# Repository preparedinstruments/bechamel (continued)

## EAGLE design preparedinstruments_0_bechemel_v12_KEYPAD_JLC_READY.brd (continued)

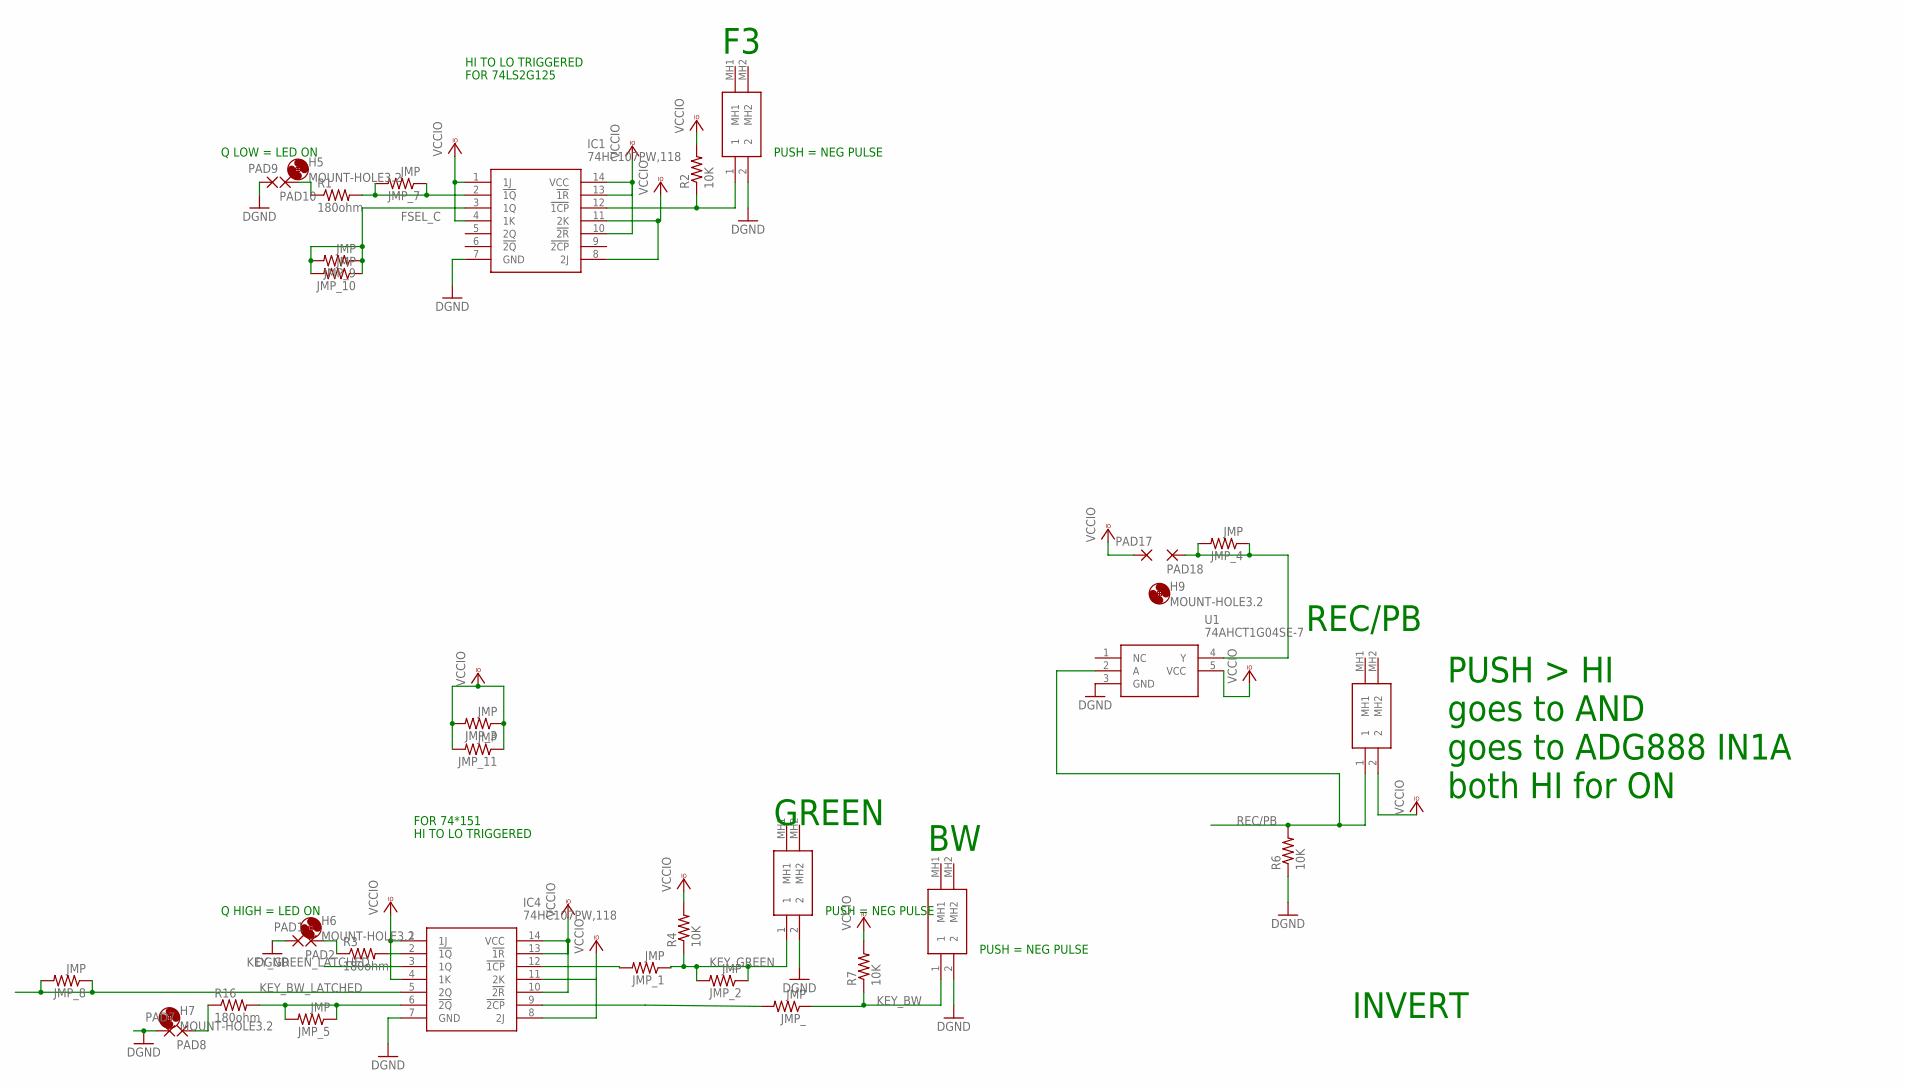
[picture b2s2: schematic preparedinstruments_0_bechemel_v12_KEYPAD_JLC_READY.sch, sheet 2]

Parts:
H5, H6, H7, H9: MOUNT-HOLE3.2; 3,2
IC1, IC4: 74HC107PW,118; SOP65P640X110-14N
JMP_, JMP_1, JMP_2, JMP_3, JMP_4, JMP_5, JMP_7, JMP_8, JMP_9, JMP_10, JMP_11: JMP; R0805
PAD1, PAD2, PAD7, PAD8, PAD9, PAD10, PAD17, PAD18: SMD2; SMD1,27-2,54
R1, R3, R16: 180ohm; R0805
R2, R4, R6, R7: 10K; R0805
S1, S2, S4, S5: MX1A-11NW; MX1A11NW
U1: 74AHCT1G04SE-7; SOT65P210X110-5N

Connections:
DGND: IC1.7 (GND), IC4.7 (GND), PAD1.1, PAD7.1, PAD9.1, R6.1, S1.2, S2.2, S4.2, U1.3 (GND); also elsewhere on the board
FSEL_C: IC1.3 (1Q), JMP_9.1, JMP_9.2, JMP_10.1, JMP_10.2; also elsewhere on the board
KEY_BW: JMP_.1, R7.1, S4.1; also elsewhere on the board
KEY_BW_LATCHED: IC4.5 (2Q), JMP_8.1, JMP_8.2; also elsewhere on the board
KEY_GREEN: JMP_1.1, JMP_2.1, JMP_2.2, R4.1, S2.1; also elsewhere on the board
KEY_GREEN_LATCHED: IC4.3 (1Q); also elsewhere on the board
unnamed: PAD10.1, R1.1
unnamed: IC1.2 (!1Q), JMP_7.1, JMP_7.2, R1.2
unnamed: JMP_4.1, JMP_4.2, PAD18.1, U1.4 (Y)
unnamed: IC1.12 (!1CP), R2.1, S1.1
unnamed: PAD2.1, R3.1
unnamed: IC4.2 (!1Q), R3.2
unnamed: PAD8.1, R16.1
unnamed: IC4.6 (!2Q), JMP_5.1, JMP_5.2, R16.2
unnamed: IC4.9 (!2CP), JMP_.2
unnamed: IC4.12 (!1CP), JMP_1.2
REC/PB: R6.2, S5.1, U1.2 (A); also elsewhere on the board
VCCIO: IC1.1 (1J), IC1.4 (1K), IC1.8 (2J), IC1.10 (!2R), IC1.11 (2K), IC1.13 (!1R), IC1.14 (VCC), IC4.1 (1J), IC4.4 (1K), IC4.8 (2J), IC4.10 (!2R), IC4.11 (2K), IC4.13 (!1R), IC4.14 (VCC), JMP_3.1, JMP_3.2, JMP_11.1, JMP_11.2, PAD17.1, R2.2, R4.2, R7.2, S5.2, U1.5 (VCC); also elsewhere on the board

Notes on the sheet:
PUSH = NEG PULSE
Q LOW = LED ON
FOR 74LS2G125
FOR 74*151
Q HIGH = LED ON
GREEN
REC/PB
PUSH > HI goes to AND goes to ADG888 IN1A both HI for ON
INVERT
HI TO LO TRIGGERED

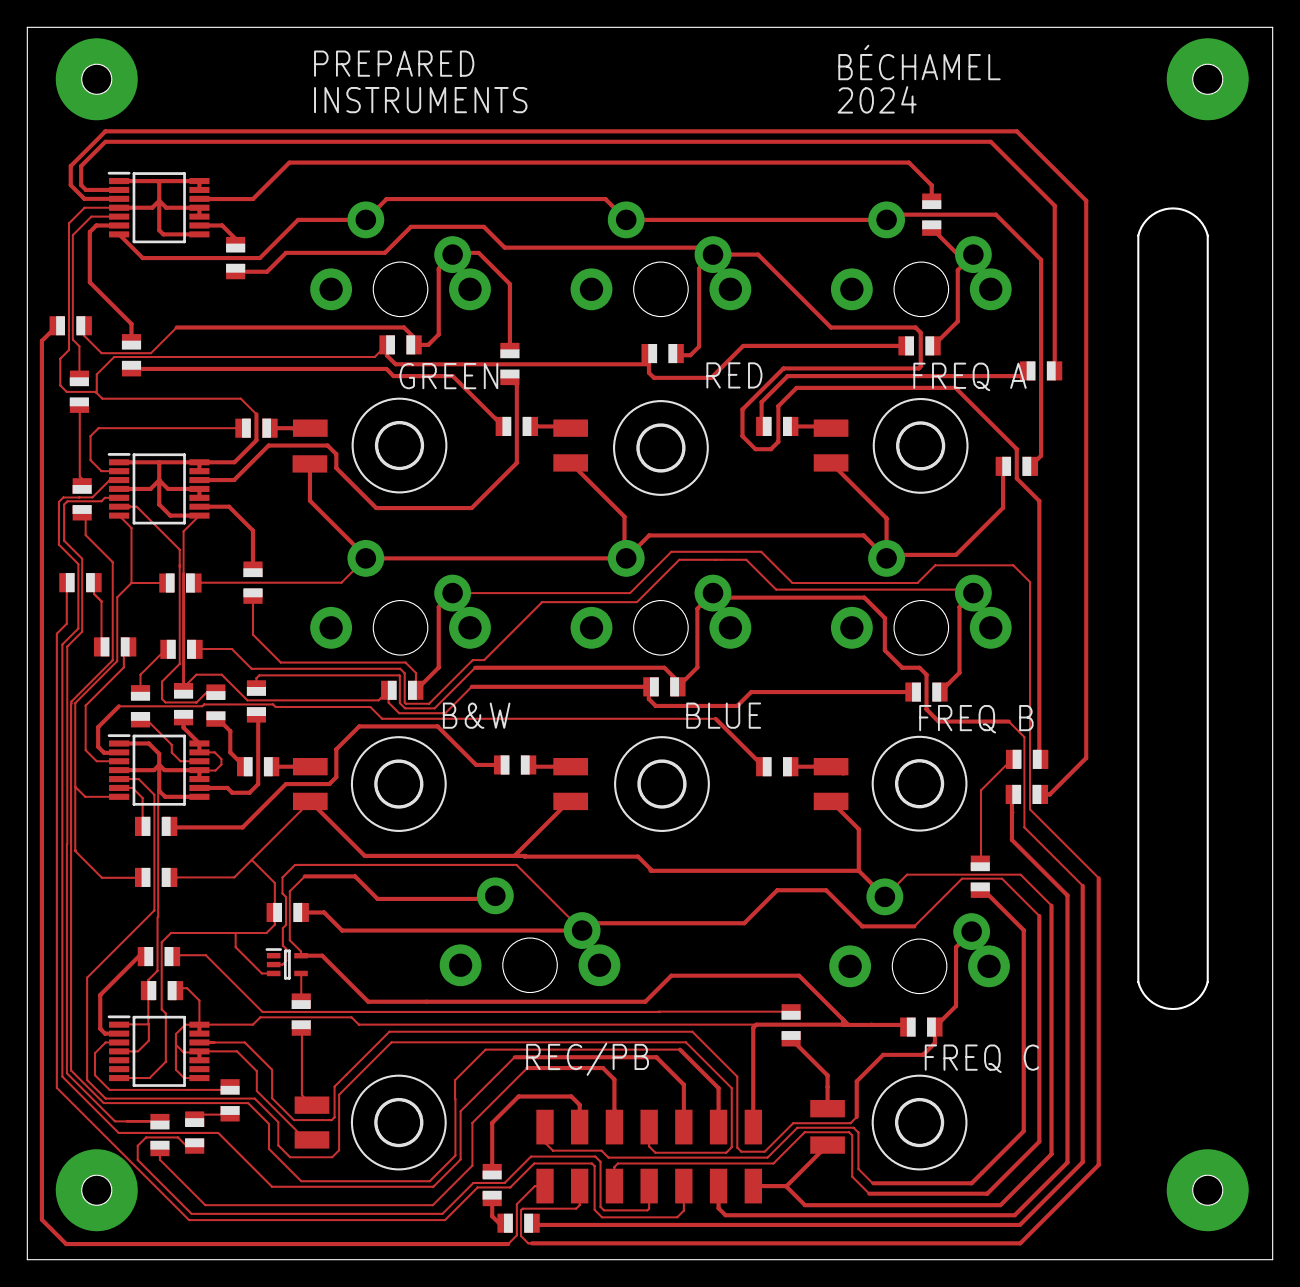
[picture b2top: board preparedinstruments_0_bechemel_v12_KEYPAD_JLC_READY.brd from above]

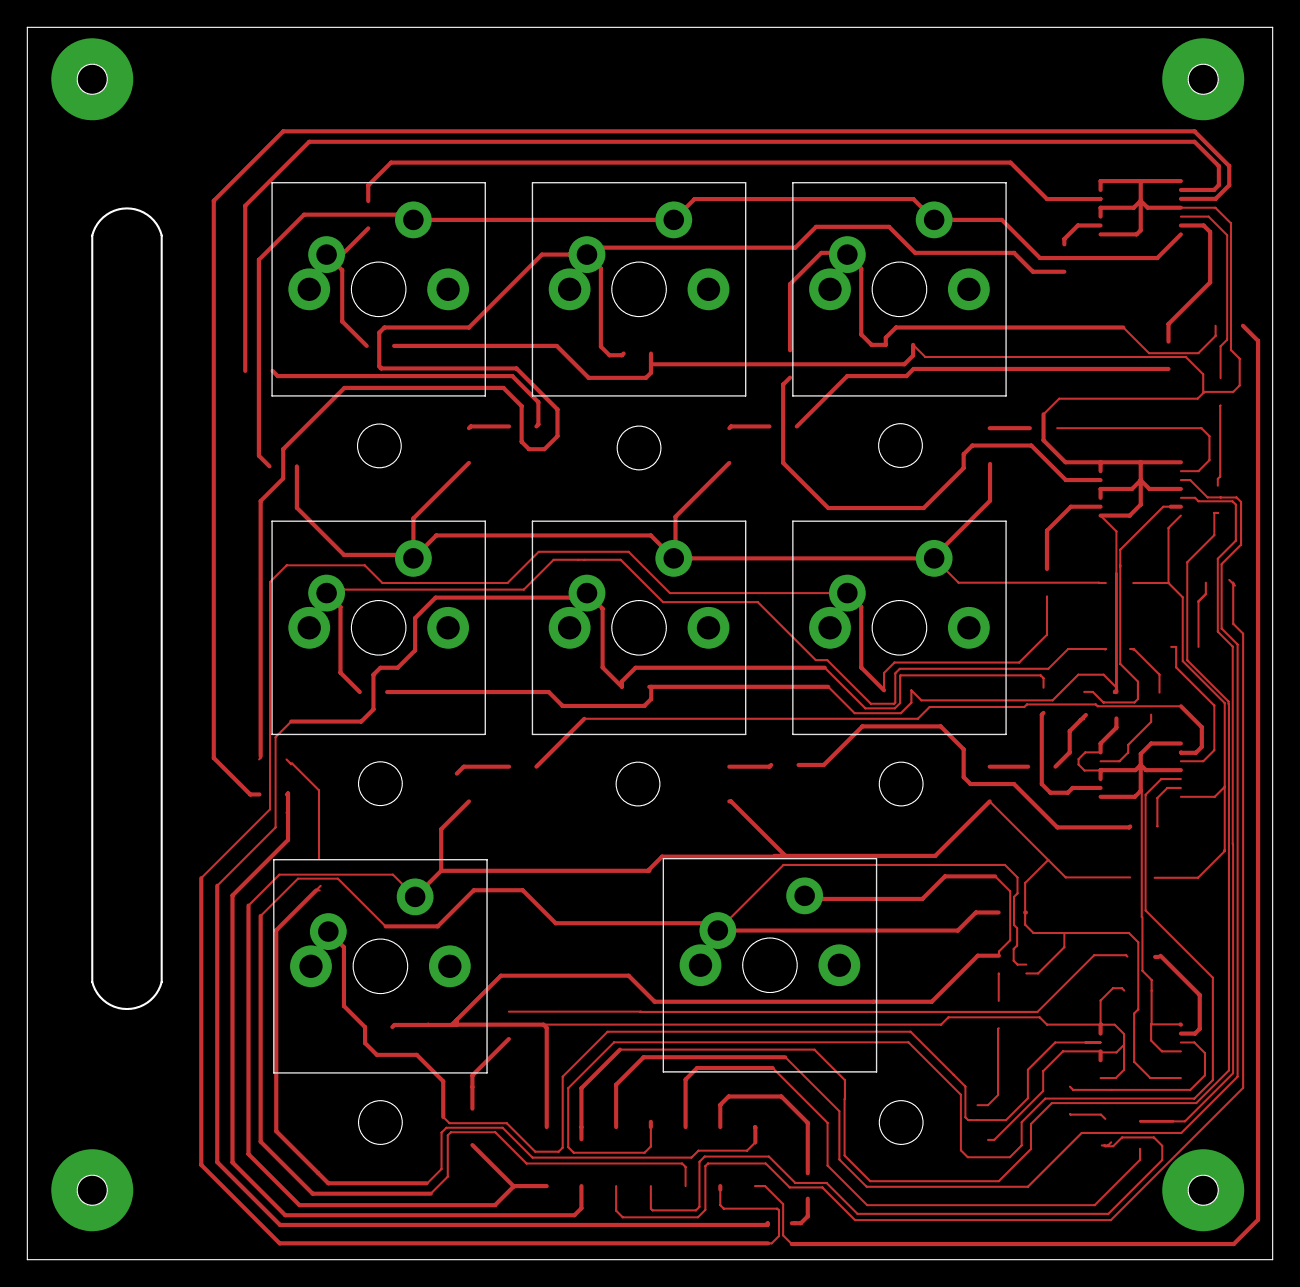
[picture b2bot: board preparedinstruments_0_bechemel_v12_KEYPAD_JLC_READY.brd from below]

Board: 2 copper layers, 91.1 x 90.2 mm, 101 parts (8 on the bottom side), 38 nets.

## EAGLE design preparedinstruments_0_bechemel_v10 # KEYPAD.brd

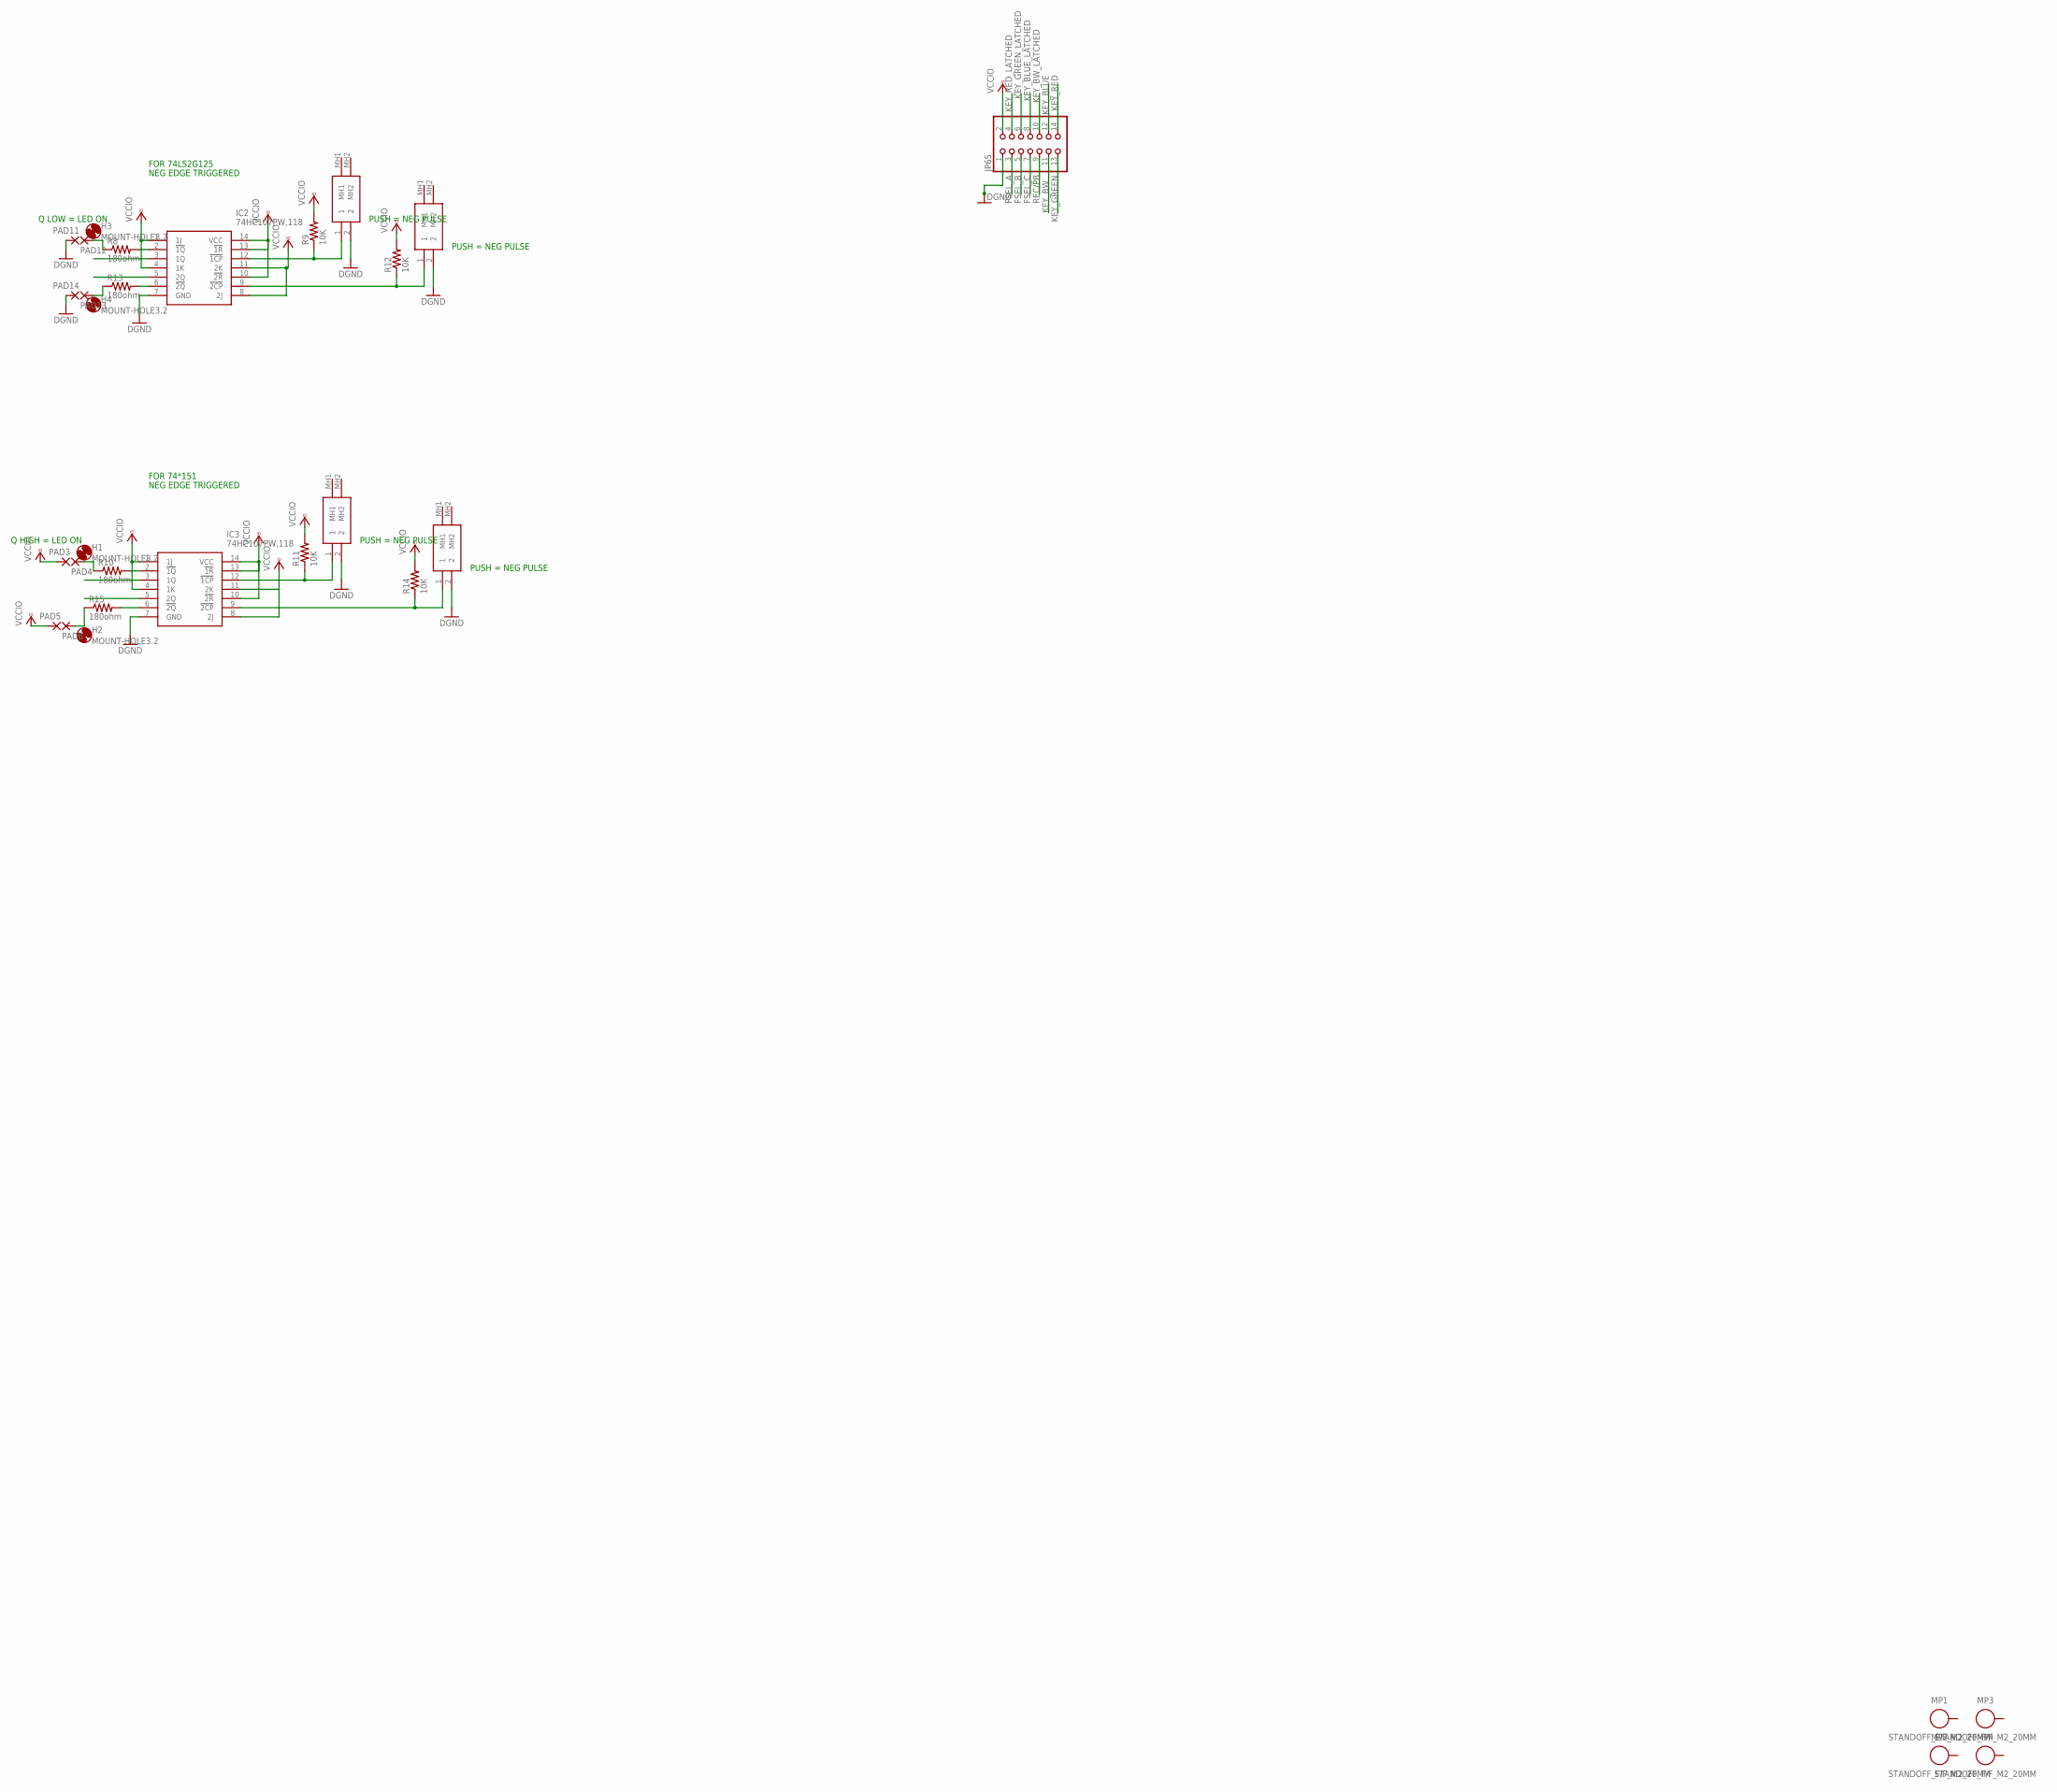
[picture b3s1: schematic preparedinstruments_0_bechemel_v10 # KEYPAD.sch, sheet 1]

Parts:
H1, H2, H3, H4: MOUNT-HOLE3.2; 3,2
IC2, IC3: 74HC107PW,118; SOP65P640X110-14N
JP65: PINHD-2X7; 2X07
MP1, MP2, MP3, MP4: STANDOFF_F/F_M2_20MM; STANDOFF_HEX_FEMALE_400X2000_M2X0.4_MTGP600H220
PAD3, PAD4, PAD5, PAD6, PAD11, PAD12, PAD13, PAD14: SMD2; SMD1,27-2,54
R8, R10, R13, R15: 180ohm; R0805
R9, R11, R12, R14: 10K; R0805
S6, S7, S8, S9: MX1A-11NW; MX1A11NW

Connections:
DGND: IC2.7 (GND), IC3.7 (GND), JP65.1, PAD11.1, PAD14.1, S6.2, S7.2, S8.2, S9.2; also elsewhere on the board
FSEL_A: JP65.3
FSEL_B: JP65.5
FSEL_C: JP65.7
KEY_BLUE: JP65.12
KEY_BLUE_LATCHED: JP65.8
KEY_BW: JP65.11
KEY_BW_LATCHED: JP65.10
KEY_GREEN: JP65.13
KEY_GREEN_LATCHED: JP65.6
KEY_RED: JP65.14
KEY_RED_LATCHED: JP65.4
unnamed: PAD12.1, R8.1
unnamed: IC2.2 (!1Q), R8.2
unnamed: IC2.12 (!1CP), R9.1, S6.1
unnamed: PAD4.1, R10.1
unnamed: IC3.2 (!1Q), R10.2
unnamed: IC3.12 (!1CP), R11.1, S7.1
unnamed: IC2.9 (!2CP), R12.1, S8.1
unnamed: PAD13.1, R13.1
unnamed: IC2.6 (!2Q), R13.2
unnamed: IC3.9 (!2CP), R14.1, S9.1
unnamed: PAD6.1, R15.1
unnamed: IC3.6 (!2Q), R15.2
REC/PB: JP65.9
VCCIO: IC2.1 (1J), IC2.4 (1K), IC2.8 (2J), IC2.10 (!2R), IC2.11 (2K), IC2.13 (!1R), IC2.14 (VCC), IC3.1 (1J), IC3.4 (1K), IC3.8 (2J), IC3.10 (!2R), IC3.11 (2K), IC3.13 (!1R), IC3.14 (VCC), JP65.2, PAD3.1, PAD5.1, R9.2, R11.2, R12.2, R14.2; also elsewhere on the board

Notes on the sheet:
NEG EDGE TRIGGERED
PUSH = NEG PULSE
Q LOW = LED ON
FOR 74LS2G125
FOR 74*151
Q HIGH = LED ON

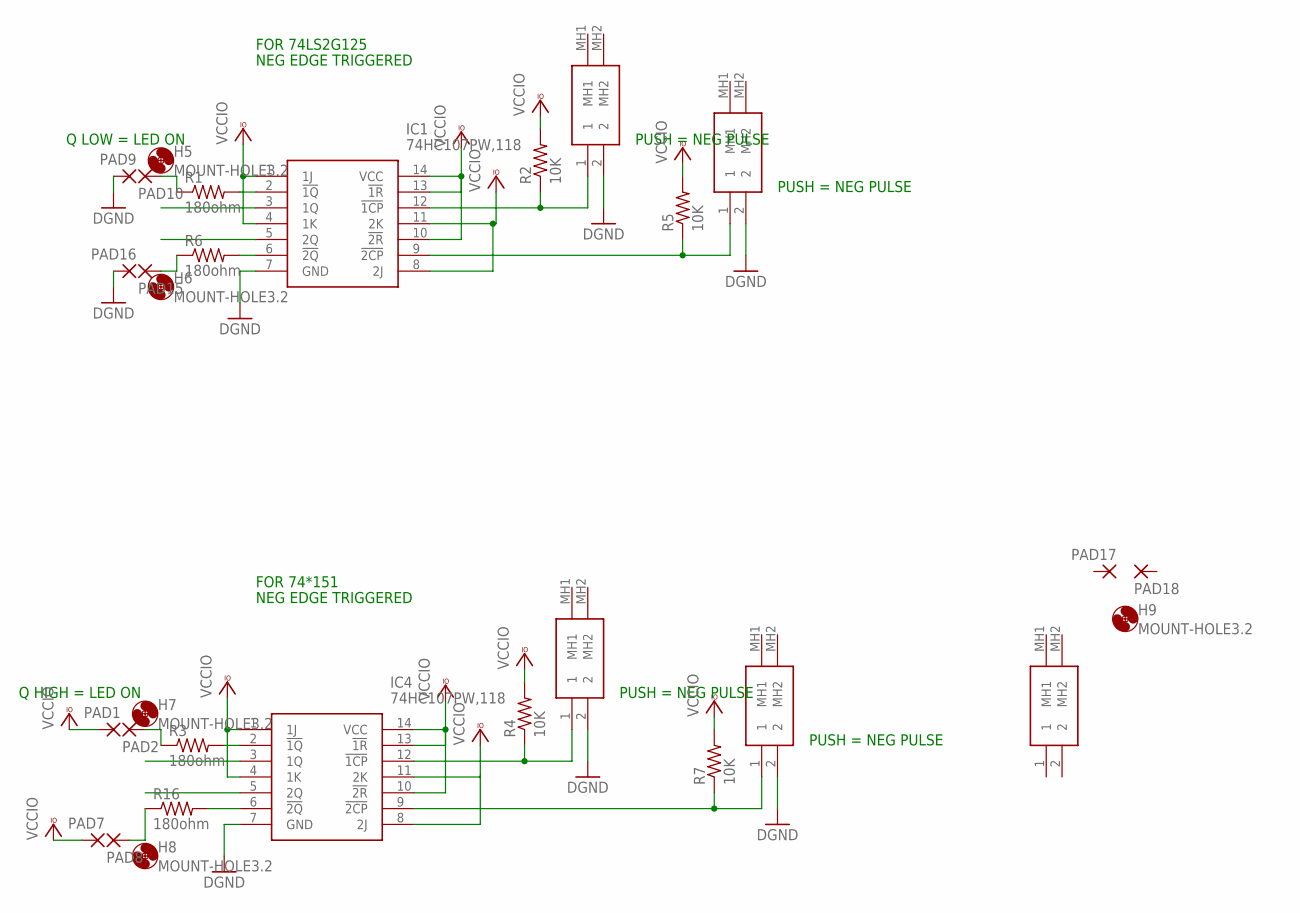
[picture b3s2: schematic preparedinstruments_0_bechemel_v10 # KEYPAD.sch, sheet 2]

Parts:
H5, H6, H7, H8, H9: MOUNT-HOLE3.2; 3,2
IC1, IC4: 74HC107PW,118; SOP65P640X110-14N
PAD1, PAD2, PAD7, PAD8, PAD9, PAD10, PAD15, PAD16, PAD17, PAD18: SMD2; SMD1,27-2,54
R1, R3, R6, R16: 180ohm; R0805
R2, R4, R5, R7: 10K; R0805
S1, S2, S3, S4, S5: MX1A-11NW; MX1A11NW

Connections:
DGND: IC1.7 (GND), IC4.7 (GND), PAD9.1, PAD16.1, S1.2, S2.2, S3.2, S4.2; also elsewhere on the board
unnamed: PAD10.1, R1.1
unnamed: IC1.2 (!1Q), R1.2
unnamed: IC1.12 (!1CP), R2.1, S1.1
unnamed: PAD2.1, R3.1
unnamed: IC4.2 (!1Q), R3.2
unnamed: IC4.12 (!1CP), R4.1, S2.1
unnamed: IC1.9 (!2CP), R5.1, S3.1
unnamed: PAD15.1, R6.1
unnamed: IC1.6 (!2Q), R6.2
unnamed: IC4.9 (!2CP), R7.1, S4.1
unnamed: PAD8.1, R16.1
unnamed: IC4.6 (!2Q), R16.2
VCCIO: IC1.1 (1J), IC1.4 (1K), IC1.8 (2J), IC1.10 (!2R), IC1.11 (2K), IC1.13 (!1R), IC1.14 (VCC), IC4.1 (1J), IC4.4 (1K), IC4.8 (2J), IC4.10 (!2R), IC4.11 (2K), IC4.13 (!1R), IC4.14 (VCC), PAD1.1, PAD7.1, R2.2, R4.2, R5.2, R7.2; also elsewhere on the board

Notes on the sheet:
NEG EDGE TRIGGERED
PUSH = NEG PULSE
Q LOW = LED ON
FOR 74LS2G125
FOR 74*151
Q HIGH = LED ON

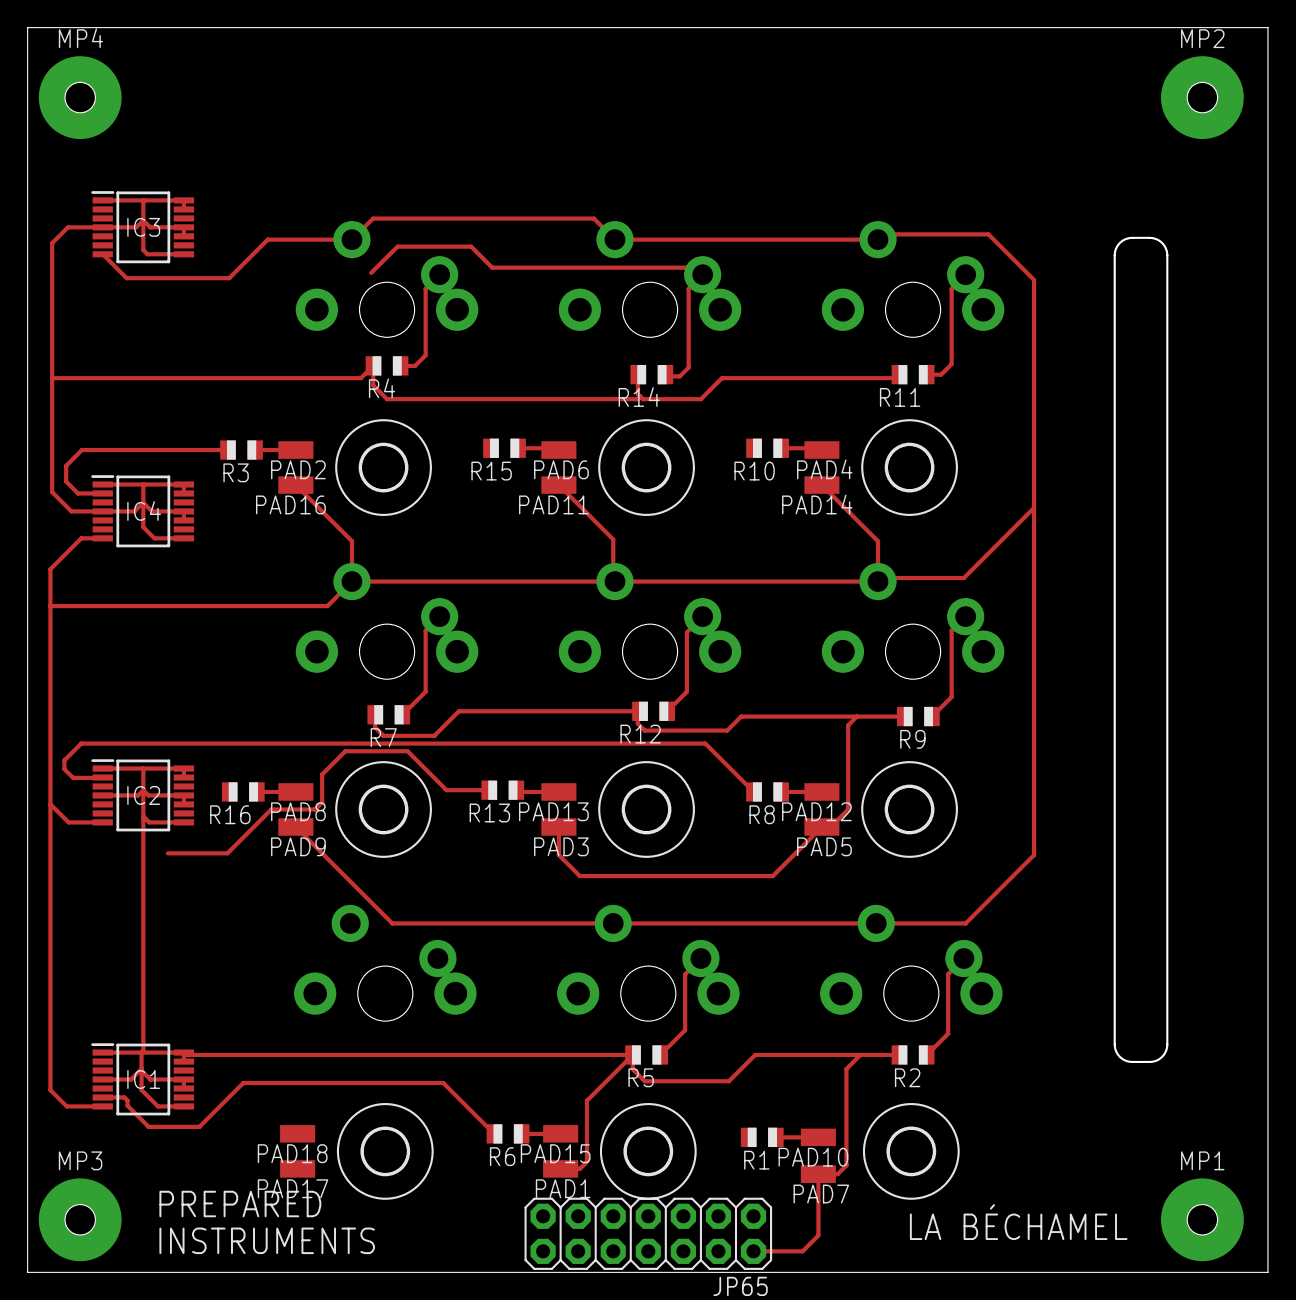
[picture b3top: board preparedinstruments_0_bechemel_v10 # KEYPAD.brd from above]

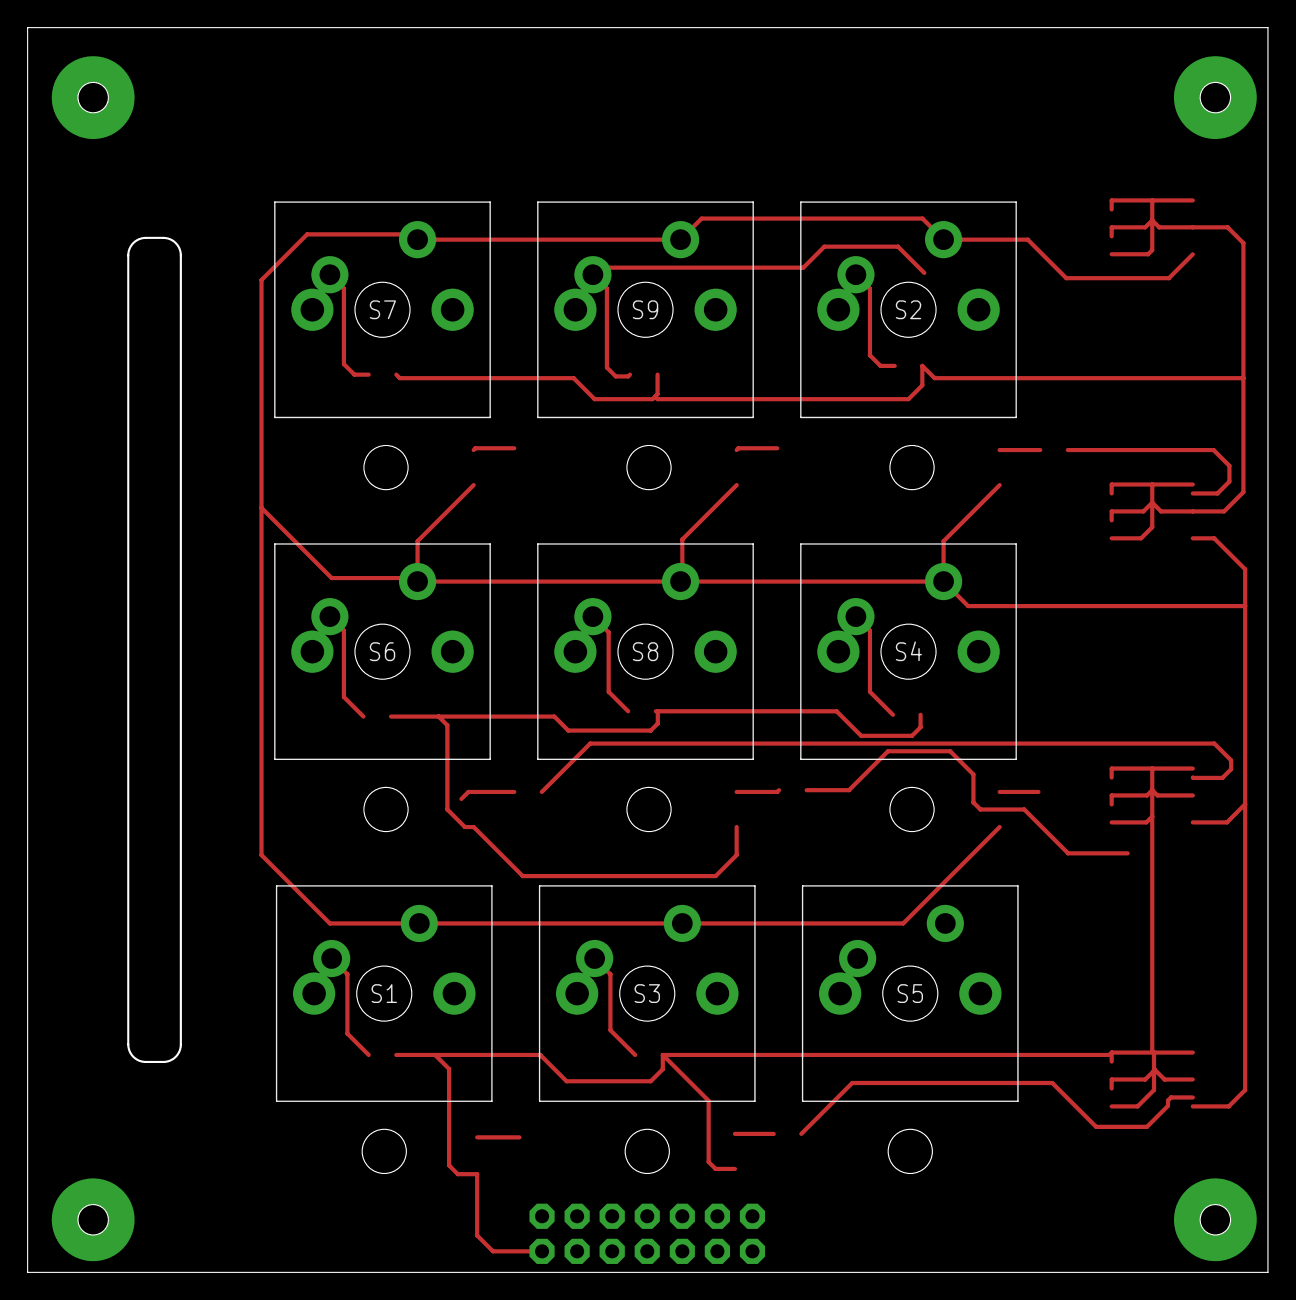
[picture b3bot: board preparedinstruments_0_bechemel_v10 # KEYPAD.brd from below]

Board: 2 copper layers, 89.8 x 90.2 mm, 61 parts (9 on the bottom side), 26 nets.
